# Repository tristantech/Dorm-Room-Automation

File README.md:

Dorm-Room-Automation
====================

Complete automation system for lights, A/V, doors, etc

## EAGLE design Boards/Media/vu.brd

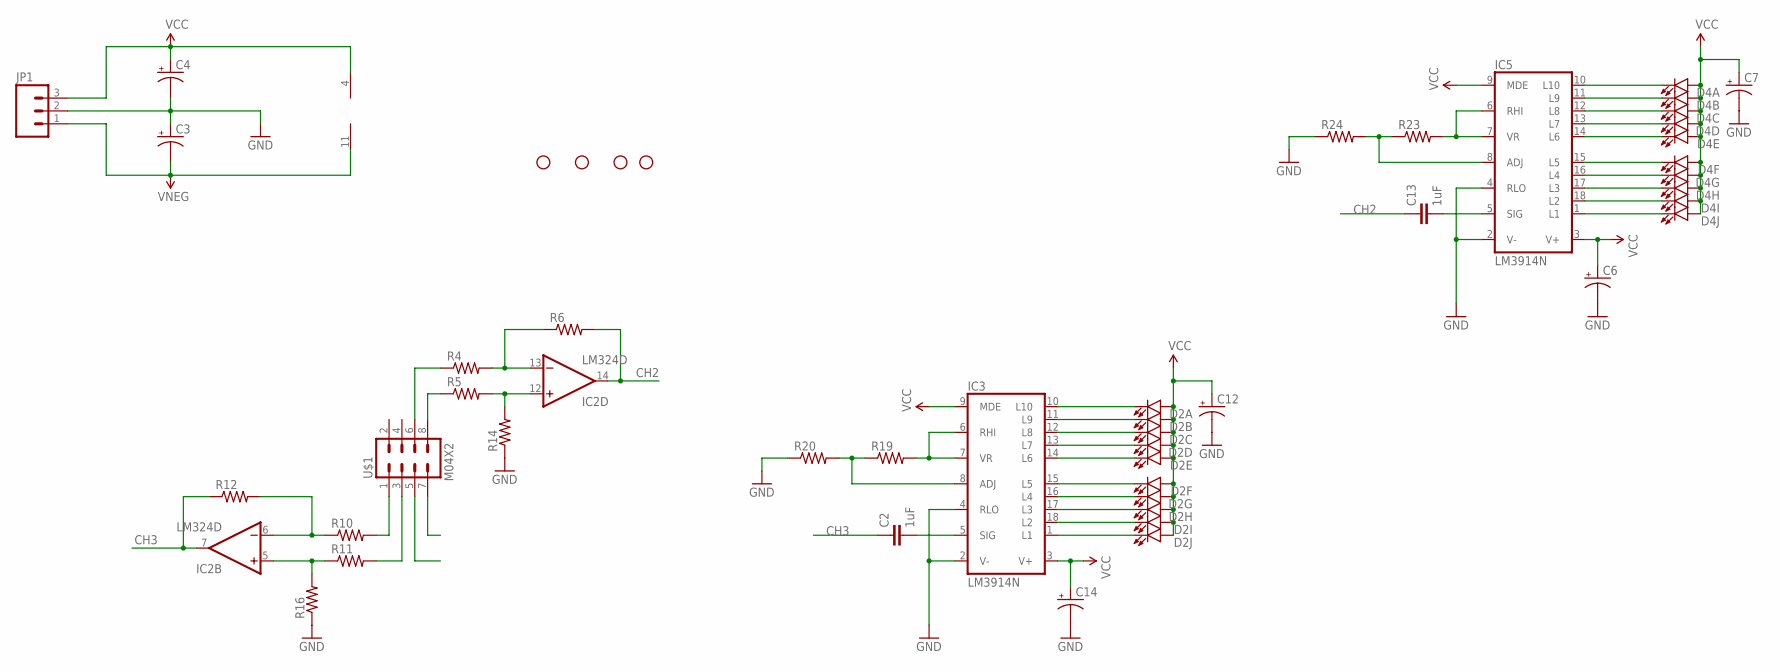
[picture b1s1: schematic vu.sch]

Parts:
C2, C13: 1uF; 1206
C3, C4: CAP_POLPTH1; CPOL-RADIAL-100UF-25V
C6, C7, C12, C14: CAP_POL1206; EIA3216
D2, D4: LED_BARGRAPH_10; LED_BARGAPH_10
IC2: LM324D; SO14
IC3, IC5: LM3914N; DIL18
JP1: M03POLAR; MOLEX-1X3
R4, R5, R6, R10, R11, R12, R14, R16: RESISTOR0603; 0603-RES
R19, R20, R23, R24: RESISTOR1206; 1206
STANDOFF1, STANDOFF2, STANDOFF3, STANDOFF4: STAND-OFF
U$1: M04X2; 2X4

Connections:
CH2: C13.1, IC2.14 (OUT), R6.2
CH3: C2.1, IC2.7 (OUT), R12.1
GND: C3.1 (+), C4.2 (-), C6.C (-), C7.C (-), C12.C (-), C14.C (-), IC3.2 (V-), IC3.4 (RLO), IC5.2 (V-), IC5.4 (RLO), JP1.2, R14.1, R16.1, R20.1, R24.1
unnamed: R11.2, U$1.3
unnamed: R10.2, U$1.1
unnamed: IC2.12 (+IN), R5.2, R14.2
unnamed: R4.1, U$1.6
unnamed: IC2.6 (-IN), R10.1, R12.2
unnamed: IC2.5 (+IN), R11.1, R16.2
unnamed: R5.1, U$1.8
unnamed: IC2.13 (-IN), R4.2, R6.1
unnamed: D2.19 (C), IC3.11 (L9)
unnamed: D2.18 (C), IC3.12 (L8)
unnamed: D2.17 (C), IC3.13 (L7)
unnamed: D2.16 (C), IC3.14 (L6)
unnamed: D2.15 (C), IC3.15 (L5)
unnamed: D2.14 (C), IC3.16 (L4)
unnamed: D2.13 (C), IC3.17 (L3)
unnamed: D2.12 (C), IC3.18 (L2)
unnamed: D2.11 (C), IC3.1 (L1)
unnamed: D2.20 (C), IC3.10 (L10)
unnamed: C2.2, IC3.5 (SIG)
unnamed: IC3.6 (RHI), IC3.7 (VR), R19.2
unnamed: IC3.8 (ADJ), R19.1, R20.2
unnamed: D4.19 (C), IC5.11 (L9)
unnamed: D4.18 (C), IC5.12 (L8)
unnamed: D4.17 (C), IC5.13 (L7)
unnamed: D4.16 (C), IC5.14 (L6)
unnamed: D4.15 (C), IC5.15 (L5)
unnamed: D4.14 (C), IC5.16 (L4)
unnamed: D4.13 (C), IC5.17 (L3)
unnamed: D4.12 (C), IC5.18 (L2)
unnamed: D4.11 (C), IC5.1 (L1)
unnamed: D4.20 (C), IC5.10 (L10)
unnamed: C13.2, IC5.5 (SIG)
unnamed: IC5.6 (RHI), IC5.7 (VR), R23.2
unnamed: IC5.8 (ADJ), R23.1, R24.2
VCC: C4.1 (+), C6.A (+), C7.A (+), C12.A (+), C14.A (+), D2.1 (A), D2.2 (A), D2.3 (A), D2.4 (A), D2.5 (A), D2.6 (A), D2.7 (A), D2.8 (A), D2.9 (A), D2.10 (A), D4.1 (A), D4.2 (A), D4.3 (A), D4.4 (A), D4.5 (A), D4.6 (A), D4.7 (A), D4.8 (A), D4.9 (A), D4.10 (A), IC2.4 (V+), IC3.3 (V+), IC3.9 (MDE), IC5.3 (V+), IC5.9 (MDE), JP1.3
VNEG: C3.2 (-), IC2.11 (V-), JP1.1

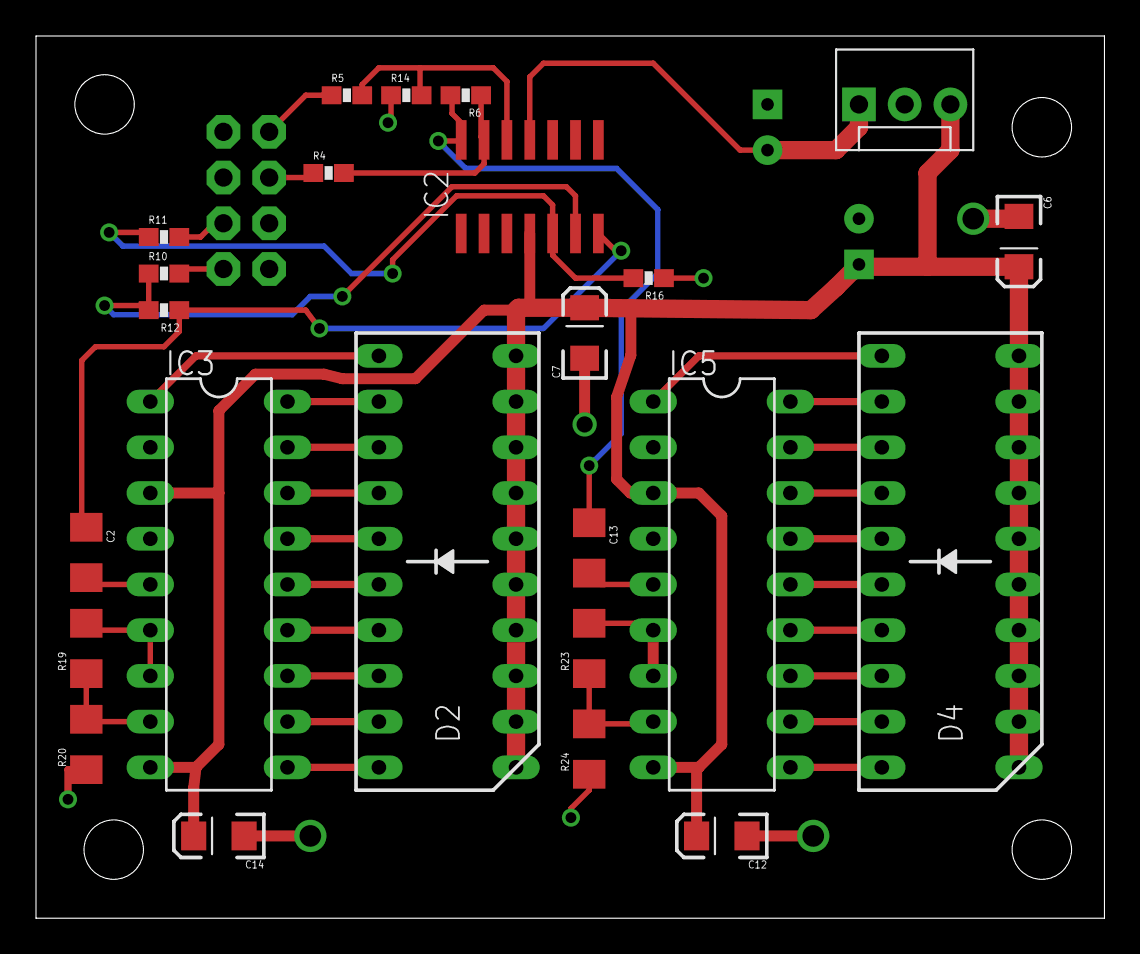
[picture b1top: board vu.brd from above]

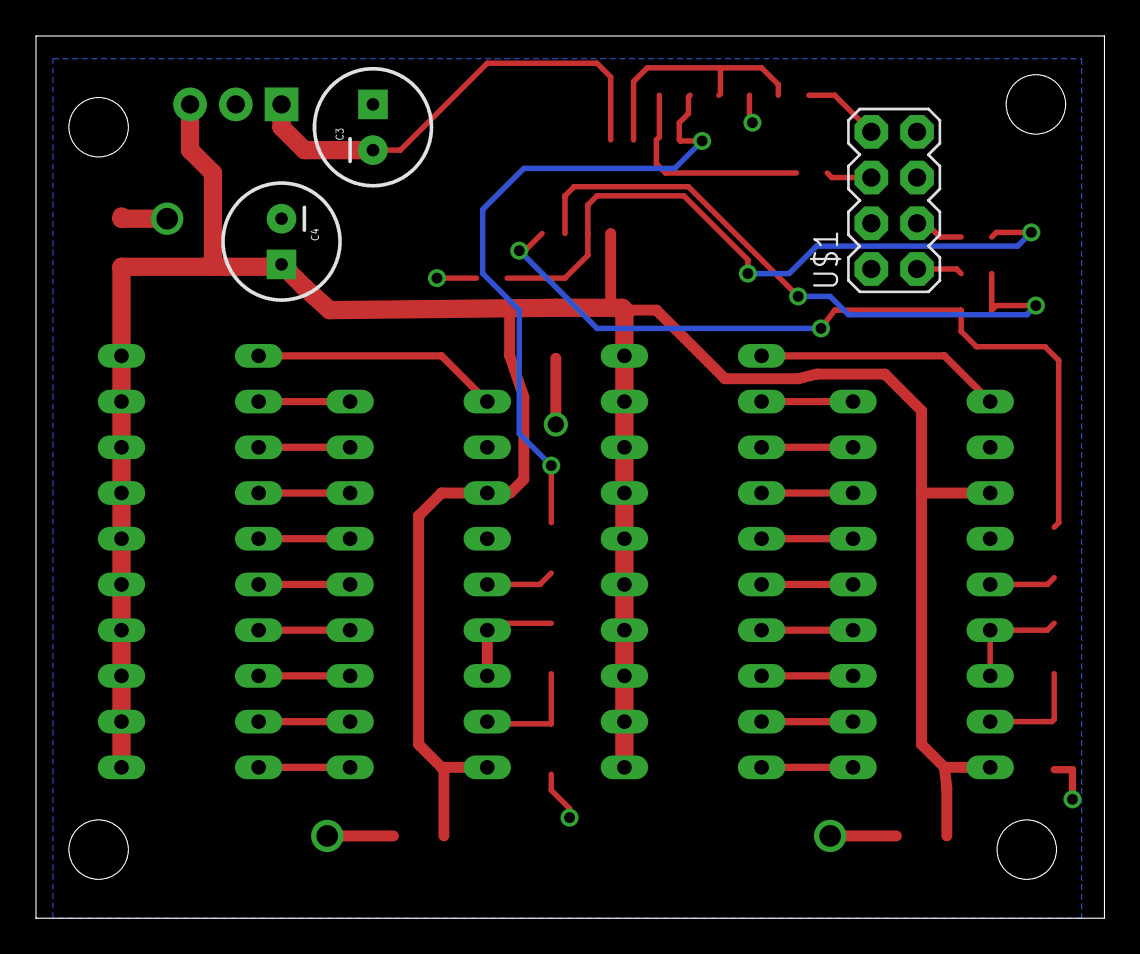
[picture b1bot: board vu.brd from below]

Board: 2 copper layers, 59.4 x 49.0 mm, 31 parts (3 on the bottom side), 39 nets.

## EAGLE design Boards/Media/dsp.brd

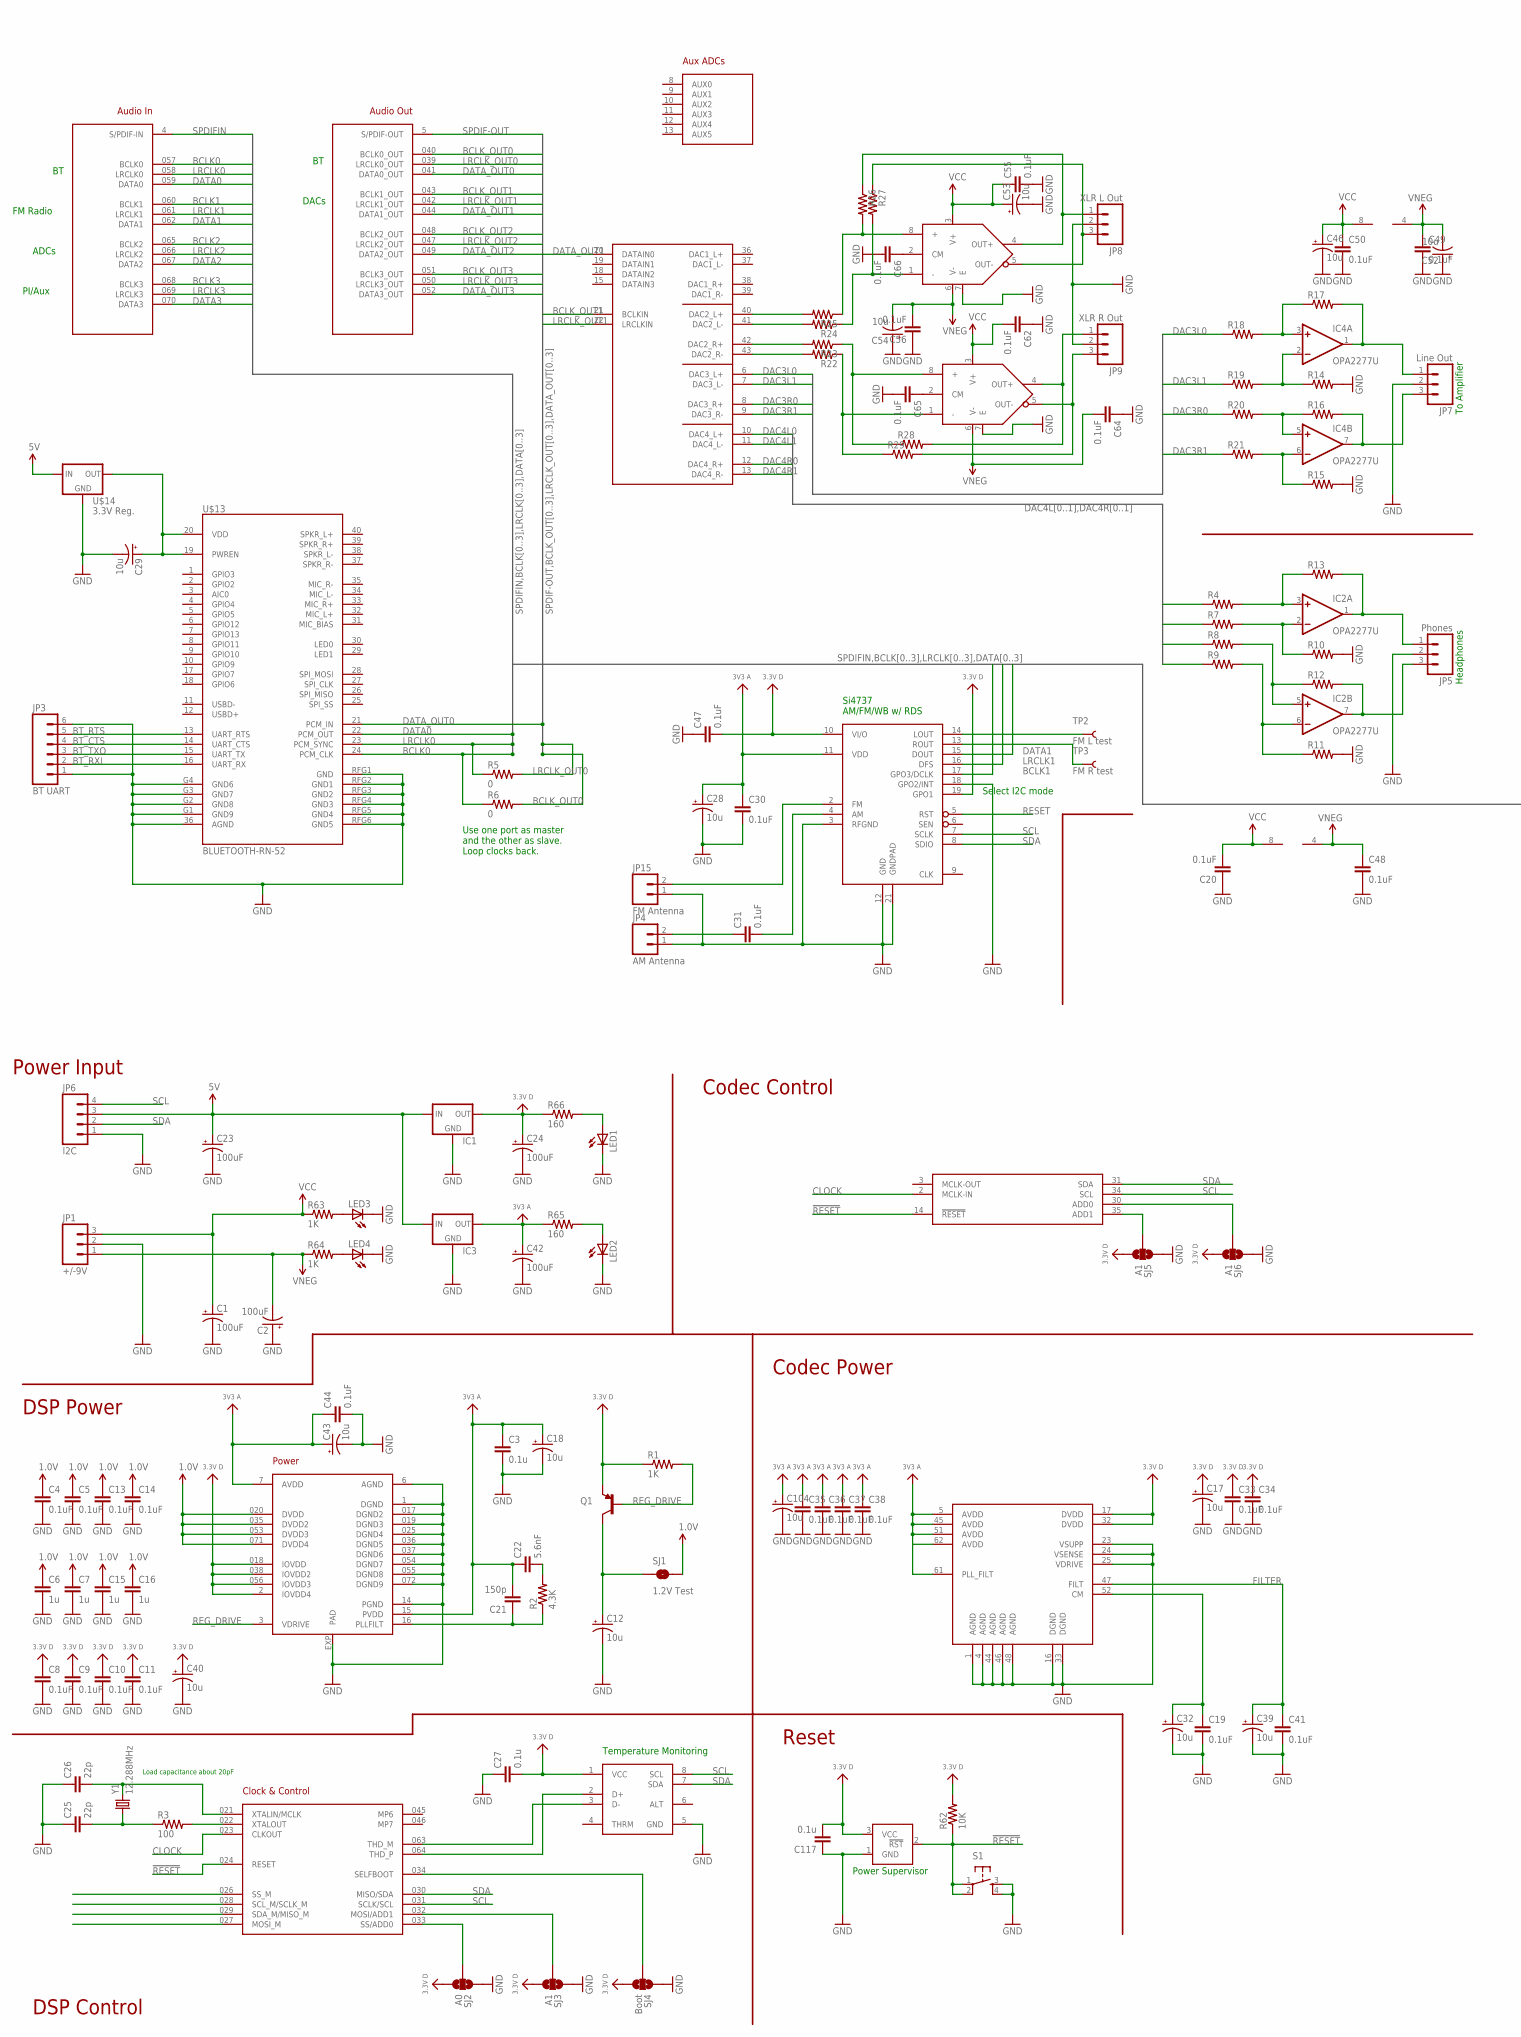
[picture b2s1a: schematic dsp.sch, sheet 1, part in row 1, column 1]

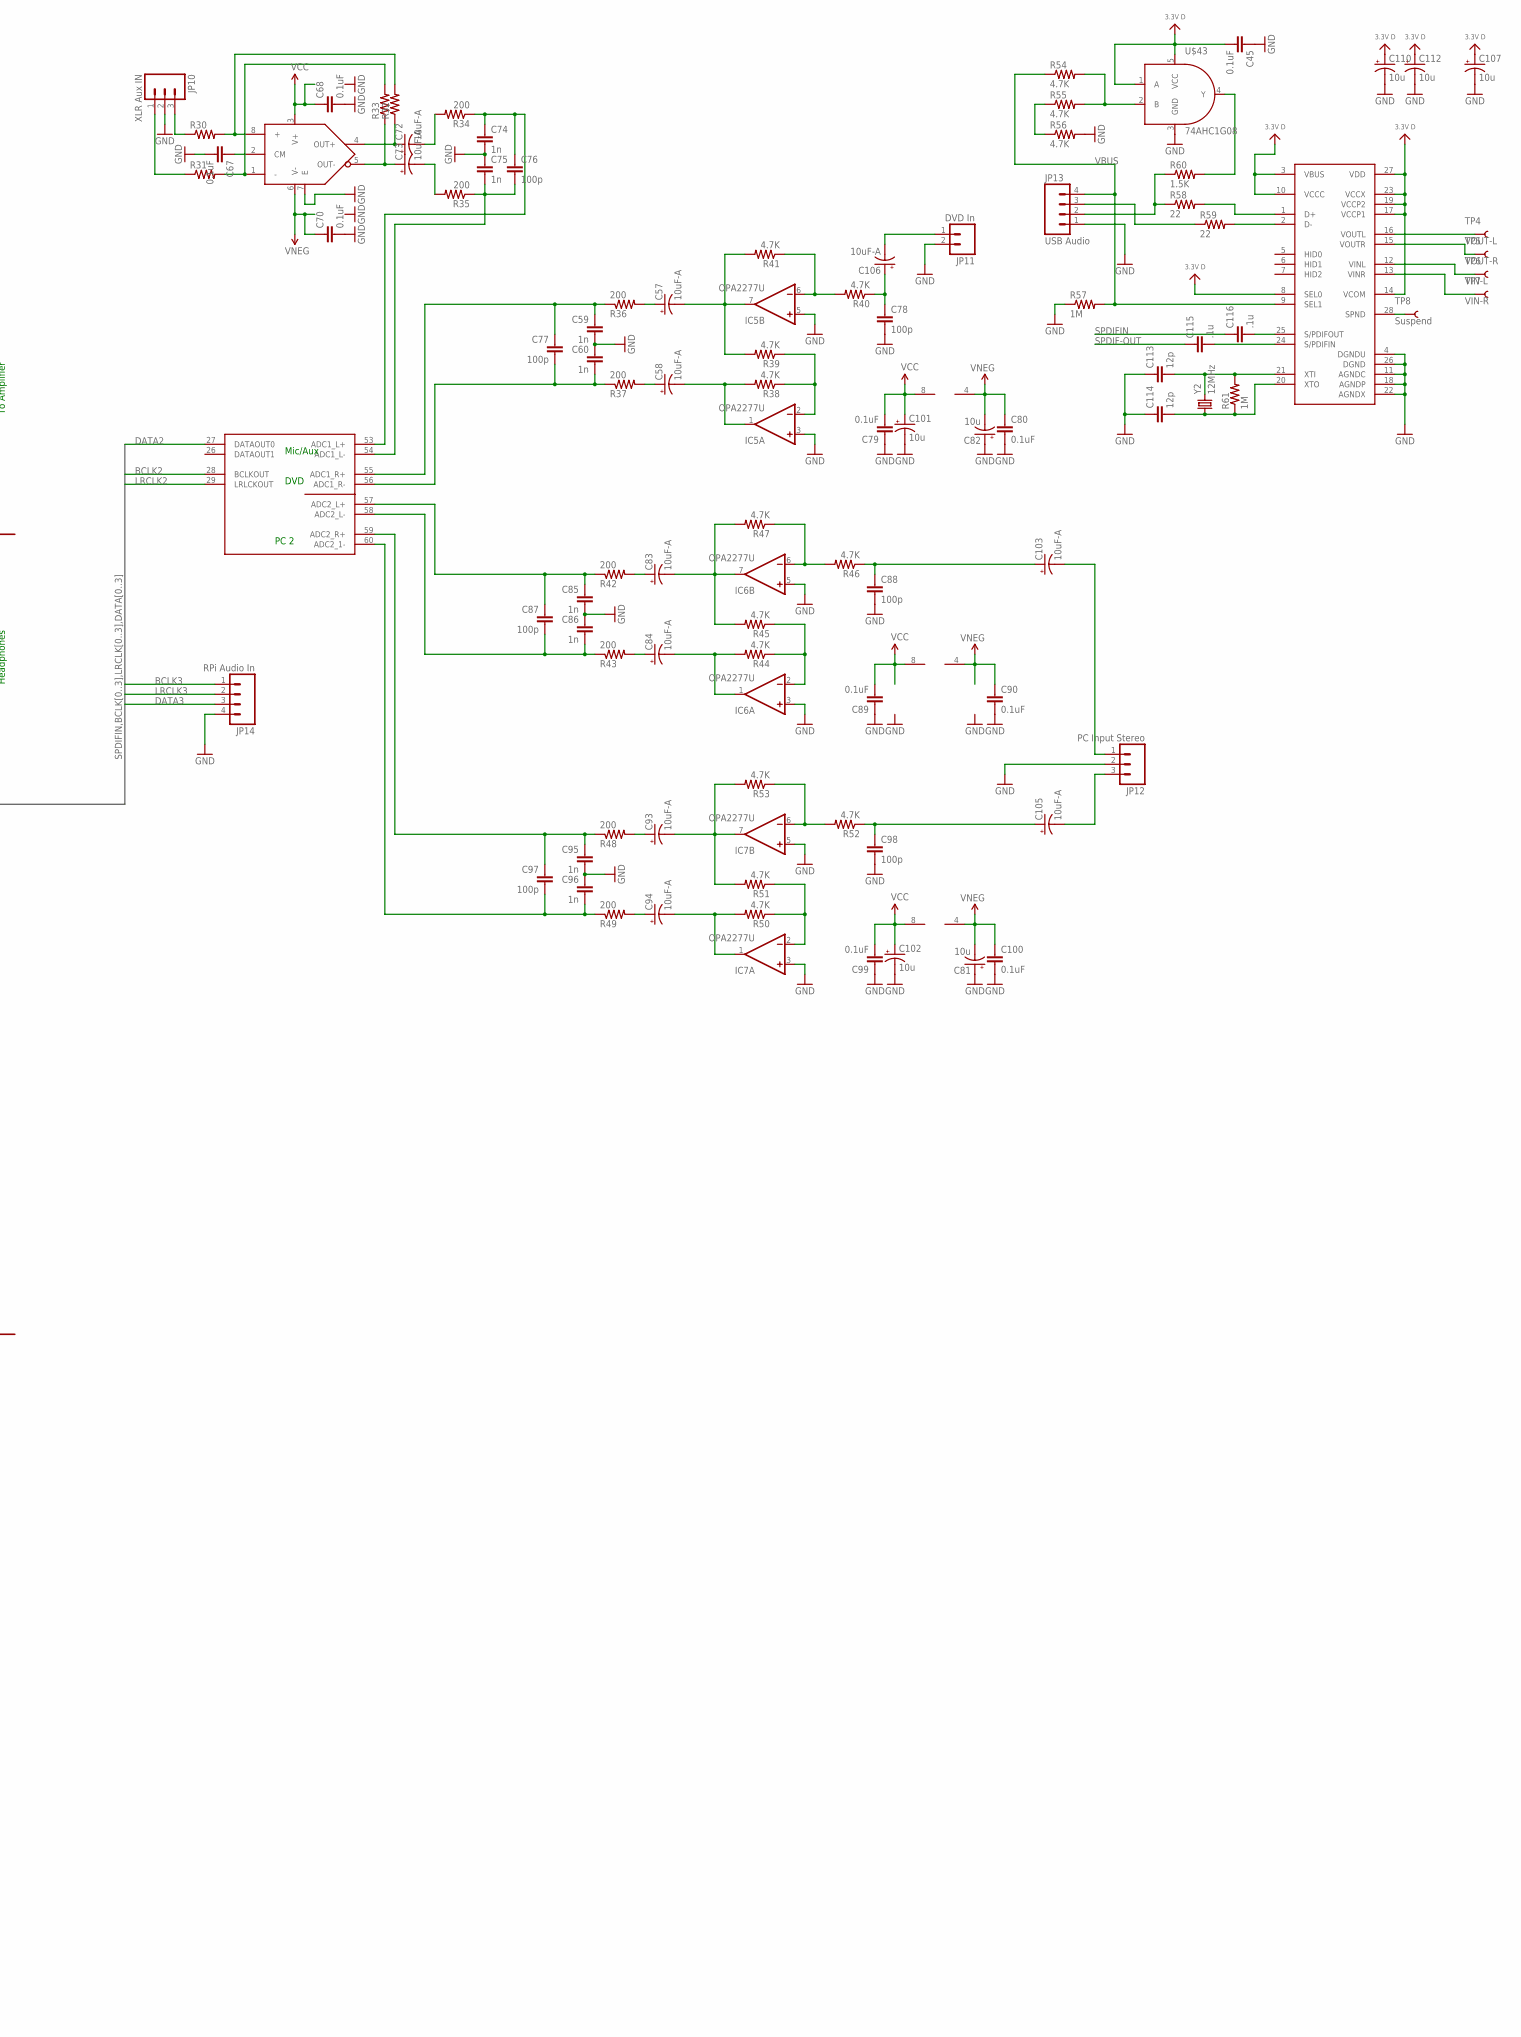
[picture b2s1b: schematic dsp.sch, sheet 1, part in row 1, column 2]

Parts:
C1, C2, C23, C24, C42: 100uF; CPOL-RADIAL-100UF-25V
C3, C27, C117: 0.1u; 0603-CAP
C4, C5, C8, C9, C10, C11, C13, C14, C19, C20, C30, C31, C33, C34, C35, C36, C37, C38, C41, C44, C45, C47, C48, C49, C50, C55, C56, C62, C64, C65, C66, C67, C68, C70, C79, C80, C89, C90, C99, C100: 0.1uF; 0603-CAP
C6, C7, C15, C16: 1u; 0603-CAP
C12, C17, C18, C28, C29, C32, C39, C40, C43, C46, C52, C53, C54, C81, C82, C101, C102, C104, C107, C110, C112: 10u; PANASONIC_B
C21: 150p; 0603-CAP
C22: 5.6nF; 0603-CAP
C25, C26: 22p; 0603-CAP
C57, C58, C72, C73, C83, C84, C93, C94, C103, C105, C106: 10uF-A; PANASONIC_C
C59, C60, C74, C75, C85, C86, C95, C96: 1n; 0603-CAP
C76, C77, C78, C87, C88, C97, C98: 100p; 0603-CAP
C113, C114: 12p; 0603-CAP
C115, C116: .1u; 0603-CAP
IC1, IC3: V_REG_78XXSINK; TO220-IGO
IC2, IC4, IC5, IC6, IC7: OPA2277U; SO08
JP1: +/-9V; MOLEX-1X3
JP3: BT UART; MOLEX-1X6
JP4: AM Antenna; 1X02
JP5: Phones; MOLEX-1X3
JP6: I2C; MOLEX-1X4
JP7: Line Out; MOLEX-1X3
JP8: XLR L Out; MOLEX-1X3
JP9: XLR R Out; MOLEX-1X3
JP10: XLR Aux IN; MOLEX-1X3
JP11: DVD In; MOLEX-1X2
JP12: PC Input Stereo; MOLEX-1X3
JP13: USB Audio; MOLEX-1X4
JP14: RPi Audio In; MOLEX-1X4
JP15: FM Antenna; 1X02
LED1, LED2, LED3, LED4: LED1206; LED-1206
Q1: TRANSISTOR_PNPSMD; SOT23-3
R1, R63, R64: 1K; 1206
R2: 4.3K; 1206
R3: 100; 1206
R4, R7, R8, R9, R10, R11, R12, R13, R14, R15, R16, R17, R18, R19, R20, R21, R22, R23, R24, R25, R26, R27, R28, R29, R30, R31, R32, R33: RESISTOR1206; 1206
R5, R6: 0; 1206
R34, R35, R36, R37, R42, R43, R48, R49: 200; 1206
R38, R39, R40, R41, R44, R45, R46, R47, R50, R51, R52, R53, R54, R55, R56: 4.7K; 1206
R57, R61: 1M; 1206
R58, R59: 22; 1206
R60: 1.5K; 1206
R62: 10K; 1206
R65, R66: 160; 1206
S1: TAC_SWITCHPTH; TACTILE-PTH
SJ1: 1.2V Test; SJ_2S-NO
SJ2: A0; SJ_3
SJ3, SJ5, SJ6: A1; SJ_3
SJ4: Boot; SJ_3
TP2: FM L test; PAD.03X.03
TP3: FM R test; PAD.03X.03
TP4: VOUT-L; PAD.03X.03
TP5: VOUT-R; PAD.03X.03
TP6: VIN-L; PAD.03X.03
TP7: VIN-R; PAD.03X.03
TP8: Suspend; PAD.03X.03
U$1: ADAU1451; LFCSP-72
U$8: ADM1032; MSOP-8
U$13: BLUETOOTH-RN-52; RN-52
U$14: 3.3V Reg.; SOT223
U$15: SI4736/37/38/39; QFN-16
U$17: AD1937; LQFP-64
U$35, U$38, U$39: LME49724; SOIC-8
U$40: PCM2903; SSOP-28
U$43: 74AHC1G08; SOT23-5
U$52: TLV803; SOT23
Y1: 12.288MHz; HC49U-V
Y2: 12MHz; HC49U-V

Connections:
1.0V: C4.1, C5.1, C6.1, C7.1, C13.1, C14.1, C15.1, C16.1, SJ1.2, U$1.020 (DVDD), U$1.035 (DVDD2), U$1.053 (DVDD3), U$1.071 (DVDD4)
3.3V_A: C3.1, C18.+, C21.2, C22.1, C28.+, C30.1, C35.1, C36.1, C37.1, C38.1, C42.1 (+), C43.+, C44.1, C104.+, IC3.OUT, R65.1, U$1.7 (AVDD), U$1.15 (PVDD), U$15.11 (VDD), U$17.5 (AVDD), U$17.45 (AVDD), U$17.51 (AVDD), U$17.61 (PLL_FILT), U$17.62 (AVDD)
3V3_D: C8.1, C9.1, C10.1, C11.1, C17.+, C24.1 (+), C27.2, C33.1, C34.1, C40.+, C45.2, C47.2, C107.+, C110.+, C112.+, C117.2, IC1.OUT, Q1.2 (E), R1.1, R62.2, R66.1, SJ2.3, SJ3.3, SJ4.3, SJ5.3, SJ6.3, U$1.2 (IOVDD4), U$1.018 (IOVDD), U$1.038 (IOVDD2), U$1.056 (IOVDD3), U$8.1 (VCC), U$15.10 (VI/O), U$15.19 (GPO1), U$17.17 (DVDD), U$17.32 (DVDD), U$40.3 (VBUS), U$40.8 (SEL0), U$40.10 (VCCC), U$40.14 (VCOM), U$40.17 (VCCP1), U$40.19 (VCCP2), U$40.23 (VCCX), U$40.27 (VDD), U$43.1 (A), U$43.5 (VCC), U$52.3 (VCC)
5V: C23.1 (+), IC1.IN, IC3.IN, JP6.3, U$14.1 (IN)
!RESET: R62.1, S1.1, S1.2, U$1.024 (RESET), U$17.14 (!RESET), U$52.2 (!RST)
BCLK0: R6.1, U$1.057 (BCLK0), U$13.24 (PCM_CLK)
BCLK1: U$1.060 (BCLK1), U$15.17 (GPO3/DCLK)
BCLK2: U$1.065 (BCLK2), U$17.28 (BCLKOUT)
BCLK3: JP14.1, U$1.068 (BCLK3)
BCLK_OUT0: R6.2, U$1.040 (BCLK0_OUT)
BCLK_OUT1: U$1.043 (BCLK1_OUT), U$17.21 (BCLKIN)
BCLK_OUT2: U$1.048 (BCLK2_OUT)
BCLK_OUT3: U$1.051 (BCLK3_OUT)
BT_CTS: JP3.4, U$13.14 (UART_CTS)
BT_RTS: JP3.5, U$13.13 (UART_RTS)
BT_RXI: JP3.2, U$13.16 (UART_RX)
BT_TXO: JP3.3, U$13.15 (UART_TX)
CLOCK: U$1.023 (CLKOUT), U$17.2 (MCLK-IN)
DAC3L0: R18.1, U$17.6 (DAC3_L+)
DAC3L1: R19.1, U$17.7 (DAC3_L-)
DAC3R0: R20.1, U$17.8 (DAC3_R+)
DAC3R1: R21.1, U$17.9 (DAC3_R-)
DAC4L0: R4.1, U$17.10 (DAC4_L+)
DAC4L1: R7.1, U$17.11 (DAC4_L-)
DAC4R0: R8.1, U$17.12 (DAC4_R+)
DAC4R1: R9.1, U$17.13 (DAC4_R-)
DATA0: U$1.059 (DATA0), U$13.22 (PCM_OUT)
DATA1: U$1.062 (DATA1), U$15.15 (DOUT)
DATA2: U$1.067 (DATA2), U$17.27 (DATAOUT0)
DATA3: JP14.3, U$1.070 (DATA3)
DATA_OUT0: U$1.041 (DATA0_OUT), U$13.21 (PCM_IN)
DATA_OUT1: U$1.044 (DATA1_OUT), U$17.20 (DATAIN0)
DATA_OUT2: U$1.049 (DATA2_OUT)
DATA_OUT3: U$1.052 (DATA3_OUT)
FILTER: C39.+, C41.1, U$17.47 (FILT)
FM: JP15.2, U$15.2 (FM)
GND: C1.2 (-), C2.1 (+), C3.2, C4.2, C5.2, C6.2, C7.2, C8.2, C9.2, C10.2, C11.2, C12.-, C13.2, C14.2, C15.2, C16.2, C17.-, C18.-, C19.2, C20.1, C23.2 (-), C24.2 (-), C25.1, C26.1, C27.1, C28.-, C29.-, C30.2, C32.-, C33.2, C34.2, C35.2, C36.2, C37.2, C38.2, C39.-, C40.-, C41.2, C42.2 (-), C43.-, C44.2, C45.1, C46.-, C47.1, C48.2, C49.2, C50.2, C52.+, C53.-, C54.+, C55.2, C56.1, C59.2, C60.1, C62.1, C64.1, C65.2, C66.2, C67.2, C68.2, C70.2, C74.2, C75.1, C78.2, C79.1, C80.2, C81.+, C82.+, C85.2, C86.1, C88.2, C89.1, C90.2, C95.2, C96.1, C98.2, C99.1, C100.2, C101.-, C102.-, C104.-, C107.-, C110.-, C112.-, C113.1, C114.1, C117.1, IC1.GND, IC3.GND, IC5.3 (+IN), IC5.5 (+IN), IC6.3 (+IN), IC6.5 (+IN), IC7.3 (+IN), IC7.5 (+IN), JP1.2, JP3.1, JP3.6, JP4.1, JP5.2, JP6.1, JP7.2, JP8.2, JP9.2, JP10.2, JP11.2, JP12.2, JP13.1, JP14.4, JP15.1, LED1.C, LED2.C, LED3.C, LED4.C, R10.2, R11.2, R14.2, R15.2, R56.2, R57.1, S1.3, S1.4, SJ2.1, SJ3.1, SJ4.1, SJ5.1, SJ6.1, U$1.1 (DGND), U$1.6 (AGND), U$1.14 (PGND), U$1.017 (DGND2), U$1.019 (DGND3), U$1.025 (DGND4), U$1.036 (DGND5), U$1.037 (DGND6), U$1.054 (DGND7), U$1.055 (DGND8), U$1.072 (DGND9), U$1.EXP (PAD), U$8.5 (GND), U$13.36 (AGND), U$13.G1 (GND9), U$13.G2 (GND8), U$13.G3 (GND7), U$13.G4 (GND6), U$13.RFG1 (GND), U$13.RFG2 (GND1), U$13.RFG3 (GND2), U$13.RFG4 (GND3), U$13.RFG5 (GND4), U$13.RFG6 (GND5), U$14.2 (GND), U$15.3 (RFGND), U$15.12 (GND), U$15.18 (GPO2/INT), U$15.21 (GNDPAD), U$17.1 (AGND), U$17.4 (AGND), U$17.16 (DGND), U$17.23 (VSUPP), U$17.24 (VSENSE), U$17.25 (VDRIVE), U$17.33 (DGND), U$17.44 (AGND), U$17.46 (AGND), U$17.48 (AGND), U$35.7 (E), U$38.7 (E), U$39.7 (E), U$40.4 (DGNDU), U$40.11 (AGNDC), U$40.18 (AGNDP), U$40.22 (AGNDX), U$40.26 (DGND), U$43.3 (GND), U$52.1 (GND)
LRCLK0: R5.1, U$1.058 (LRCLK0), U$13.23 (PCM_SYNC)
LRCLK1: U$1.061 (LRCLK1), U$15.16 (DFS)
LRCLK2: U$1.066 (LRCLK2), U$17.29 (LRLCKOUT)
LRCLK3: JP14.2, U$1.069 (LRCLK3)
LRCLK_OUT0: R5.2, U$1.039 (LRCLK0_OUT)
LRCLK_OUT1: U$1.042 (LRCLK1_OUT), U$17.22 (LRCLKIN)
LRCLK_OUT2: U$1.047 (LRCLK2_OUT)
LRCLK_OUT3: U$1.050 (LRCLK3_OUT)
unnamed: C21.1, R2.1, U$1.16 (PLLFILT)
unnamed: C22.2, R2.2
unnamed: R3.2, U$1.022 (XTALOUT)
unnamed: C12.+, Q1.3 (C), SJ1.1
unnamed: C26.2, U$1.021 (XTALIN/MCLK), Y1.2
unnamed: C25.2, R3.1, Y1.1
unnamed: C19.1, C32.+, U$17.52 (CM)
unnamed: U$1.063 (THD_M), U$8.3 (D-)
unnamed: U$1.064 (THD_P), U$8.2 (D+)
unnamed: SJ4.2, U$1.034 (SELFBOOT)
unnamed: SJ3.2, U$1.032 (MOSI/ADD1)
unnamed: SJ2.2, U$1.033 (SS/ADD0)
unnamed: C29.+, U$13.19 (PWREN), U$13.20 (VDD), U$14.3 (OUT)
unnamed: IC2.1 (OUT), JP5.1, R13.2
unnamed: IC2.3 (+IN), R4.2, R13.1
unnamed: C31.2, U$15.4 (AM)
unnamed: C31.1, JP4.2
unnamed: TP2.P$1, U$15.14 (LOUT)
unnamed: TP3.P$1, U$15.13 (ROUT)
unnamed: IC2.2 (-IN), R7.2, R10.1
unnamed: SJ5.2, U$17.35 (ADD1)
unnamed: SJ6.2, U$17.30 (ADD0)
unnamed: IC2.5 (+IN), R8.2, R12.1
unnamed: IC2.6 (-IN), R9.2, R11.1
unnamed: IC4.7 (OUT), JP7.3, R16.2
unnamed: IC4.1 (OUT), JP7.1, R17.2
unnamed: IC2.7 (OUT), JP5.3, R12.2
unnamed: IC4.3 (+IN), R17.1, R18.2
unnamed: IC4.2 (-IN), R14.1, R19.2
unnamed: IC4.5 (+IN), R16.1, R20.2
unnamed: IC4.6 (-IN), R15.1, R21.2
unnamed: C73.+, R33.1, U$39.5 (OUT-)
unnamed: JP9.1, R28.2, U$38.4 (OUT+)
unnamed: JP9.3, R29.2, U$38.5 (OUT-)
unnamed: JP8.1, R26.1, U$35.4 (OUT+)
unnamed: JP8.3, R27.1, U$35.5 (OUT-)
unnamed: R24.2, U$17.41 (DAC2_L-)
unnamed: C66.1, U$35.2 (CM)
unnamed: C65.1, U$38.2 (CM)
unnamed: R25.2, U$17.40 (DAC2_L+)
unnamed: R23.2, U$17.42 (DAC2_R+)
unnamed: R22.2, U$17.43 (DAC2_R-)
unnamed: C72.+, R32.1, U$39.4 (OUT+)
unnamed: R25.1, R26.2, U$35.8 (+)
unnamed: R24.1, R27.2, U$35.1 (-)
unnamed: R23.1, R28.1, U$38.8 (+)
unnamed: R22.1, R29.1, U$38.1 (-)
unnamed: C67.1, U$39.2 (CM)
unnamed: C72.-, R34.2
unnamed: C73.-, R35.2
unnamed: C57.+, R36.2
unnamed: R30.2, R32.2, U$39.8 (+)
unnamed: JP10.3, R30.1
unnamed: JP10.1, R31.1
unnamed: R31.2, R33.2, U$39.1 (-)
unnamed: C75.2, C76.2, R35.1, U$17.54 (ADC1_L-)
unnamed: C58.+, R37.2
unnamed: C74.1, C76.1, R34.1, U$17.53 (ADC1_L+)
unnamed: C60.2, C77.2, R37.1, U$17.56 (ADC1_R-)
unnamed: C59.1, C77.1, R36.1, U$17.55 (ADC1_R+)
unnamed: C58.-, IC5.1 (OUT), R38.2
unnamed: C57.-, IC5.7 (OUT), R39.2, R41.2
unnamed: IC5.2 (-IN), R38.1, R39.1
unnamed: IC5.6 (-IN), R40.2, R41.1
unnamed: C106.-, JP11.1
unnamed: C83.+, R42.2
unnamed: C86.2, C87.2, R43.1, U$17.58 (ADC2_L-)
unnamed: C85.1, C87.1, R42.1, U$17.57 (ADC2_L+)
unnamed: C84.+, R43.2
unnamed: C83.-, IC6.7 (OUT), R45.2, R47.2
unnamed: C84.-, IC6.1 (OUT), R44.2
unnamed: IC6.2 (-IN), R44.1, R45.1
unnamed: IC6.6 (-IN), R46.2, R47.1
unnamed: C88.1, C103.+, R46.1
unnamed: C93.+, R48.2
unnamed: C96.2, C97.2, R49.1, U$17.60 (ADC2_1-)
unnamed: C95.1, C97.1, R48.1, U$17.59 (ADC2_R+)
unnamed: C94.+, R49.2
unnamed: C93.-, IC7.7 (OUT), R51.2, R53.2
unnamed: C94.-, IC7.1 (OUT), R50.2
unnamed: IC7.2 (-IN), R50.1, R51.1
unnamed: IC7.6 (-IN), R52.2, R53.1
unnamed: C98.1, C105.+, R52.1
unnamed: C103.-, JP12.1
unnamed: C105.-, JP12.3
unnamed: C78.1, C106.+, R40.1
unnamed: TP4.P$1, U$40.16 (VOUTL)
unnamed: TP5.P$1, U$40.15 (VOUTR)
unnamed: TP6.P$1, U$40.12 (VINL)
unnamed: TP7.P$1, U$40.13 (VINR)
unnamed: JP13.2, R58.1, R60.1
unnamed: R58.2, U$40.1 (D+)
unnamed: R54.2, R55.2, U$43.2 (B)
unnamed: R59.2, U$40.2 (D-)
unnamed: R55.1, R56.1
unnamed: JP13.3, R59.1
unnamed: R60.2, U$43.4 (Y)
unnamed: C113.2, R61.2, U$40.21 (XTI), Y2.2
unnamed: TP8.P$1, U$40.28 (SPND)
unnamed: C114.2, R61.1, U$40.20 (XTO), Y2.1
unnamed: C115.2, U$40.24 (S/PDIFIN)
unnamed: C116.2, U$40.25 (S/PDIFOUT)
unnamed: LED3.A, R63.2
unnamed: LED4.A, R64.2
unnamed: LED1.A, R66.2
unnamed: LED2.A, R65.2
REG_DRIVE: Q1.1 (B), R1.2, U$1.3 (VDRIVE)
RESET: U$15.5 (RST)
SCL: JP6.4, U$1.031 (SCLK/SCL), U$8.8 (SCL), U$15.7 (SCLK), U$17.34 (SCL)
SDA: JP6.2, U$1.030 (MISO/SDA), U$8.7 (SDA), U$15.8 (SDIO), U$17.31 (SDA)
SPDIF-OUT: C115.1, U$1.5 (S/PDIF-OUT)
SPDIFIN: C116.1, U$1.4 (S/PDIF-IN)
VBUS: JP13.4, R54.1, R57.2, U$40.9 (SEL1)
VCC: C1.1 (+), C20.2, C46.+, C50.1, C53.+, C55.1, C62.2, C68.1, C79.2, C89.2, C99.2, C101.+, C102.+, IC2.8 (V+), IC4.8 (V+), IC5.8 (V+), IC6.8 (V+), IC7.8 (V+), JP1.3, R63.1, U$35.3 (V+), U$38.3 (V+), U$39.3 (V+)
VNEG: C2.2 (-), C48.1, C49.1, C52.-, C54.-, C56.2, C64.2, C70.1, C80.1, C81.-, C82.-, C90.1, C100.1, IC2.4 (V-), IC4.4 (V-), IC5.4 (V-), IC6.4 (V-), IC7.4 (V-), JP1.1, R64.1, U$35.6 (V-), U$38.6 (V-), U$39.6 (V-)

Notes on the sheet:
Load capacitance about 20pF
Temperature Monitoring
Use one port as master and the other as slave. Loop clocks back.
Si4737 AM/FM/WB w/ RDS
FM Radio
Select I2C mode
Power Input
DSP Power
DSP Control
Codec Power
Codec Control
Headphones
To Amplifier
Mic/Aux
PC 2
DVD
ADCs
DACs
Reset
PI/Aux
Power Supervisor

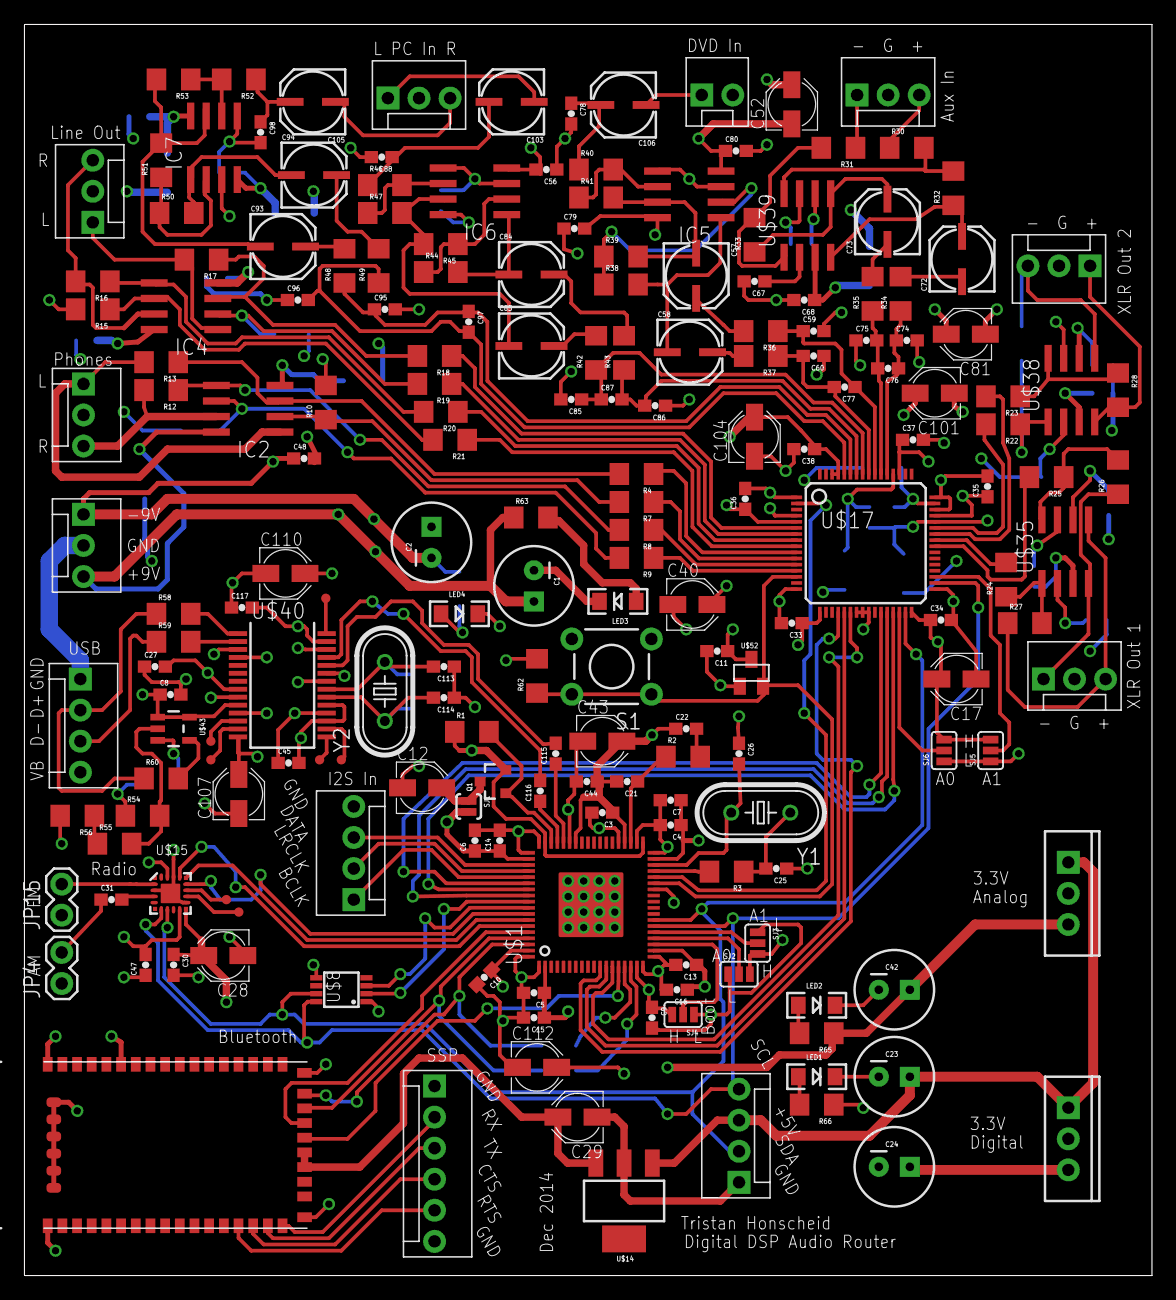
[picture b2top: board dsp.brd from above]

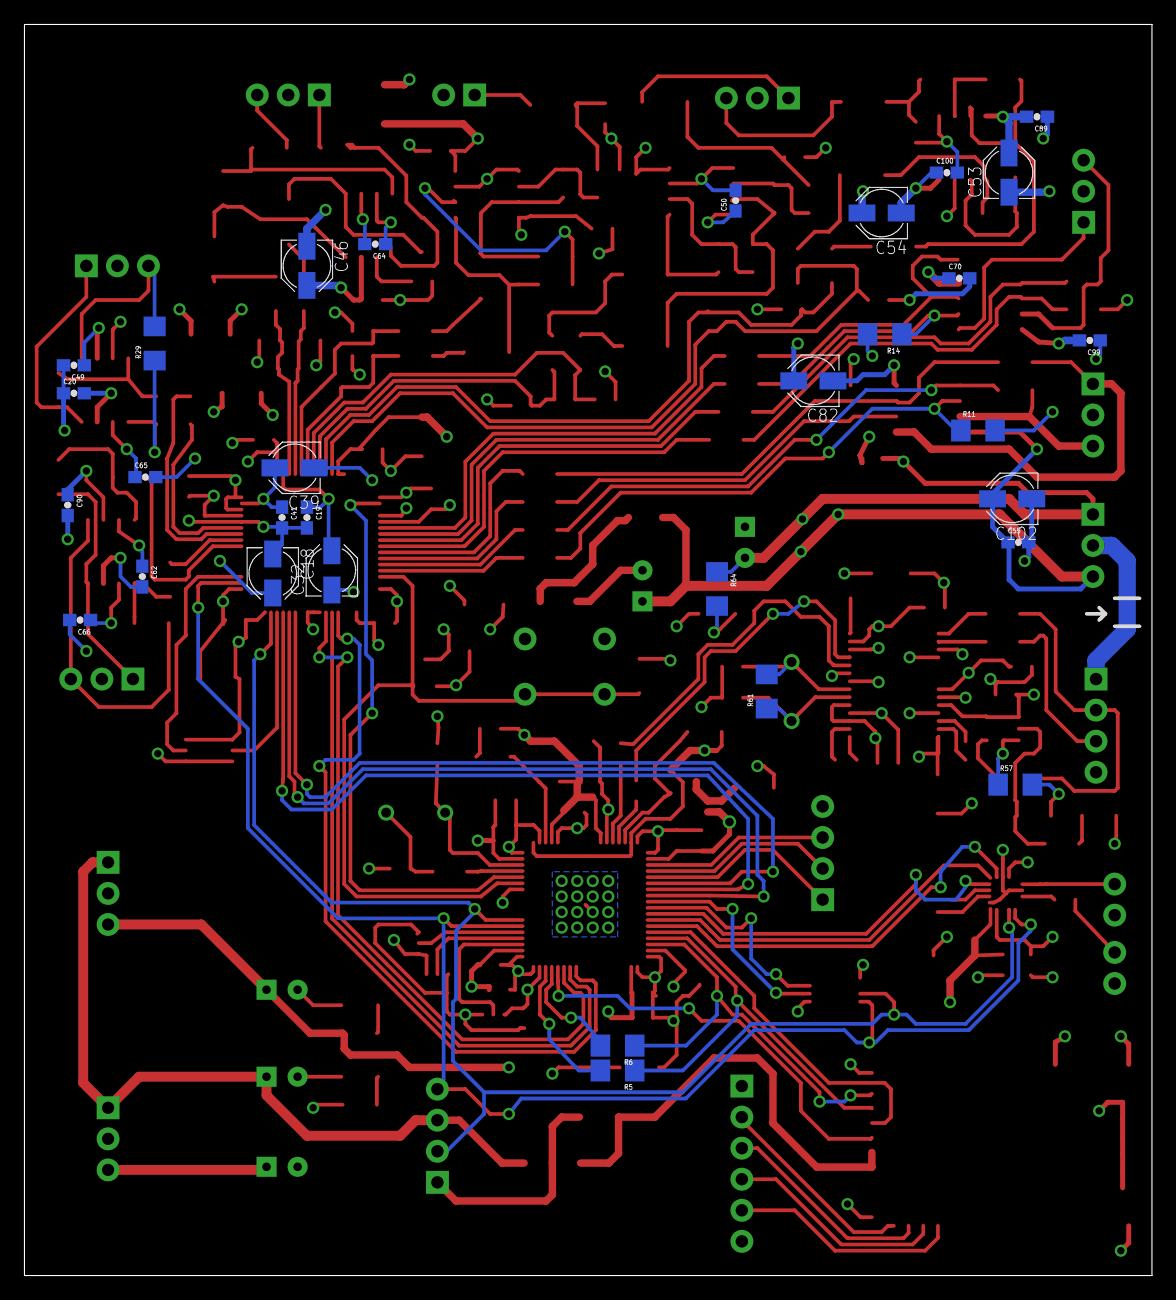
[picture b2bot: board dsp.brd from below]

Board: 4 copper layers, 92.2 x 102.3 mm, 227 parts (31 on the bottom side), 153 nets.

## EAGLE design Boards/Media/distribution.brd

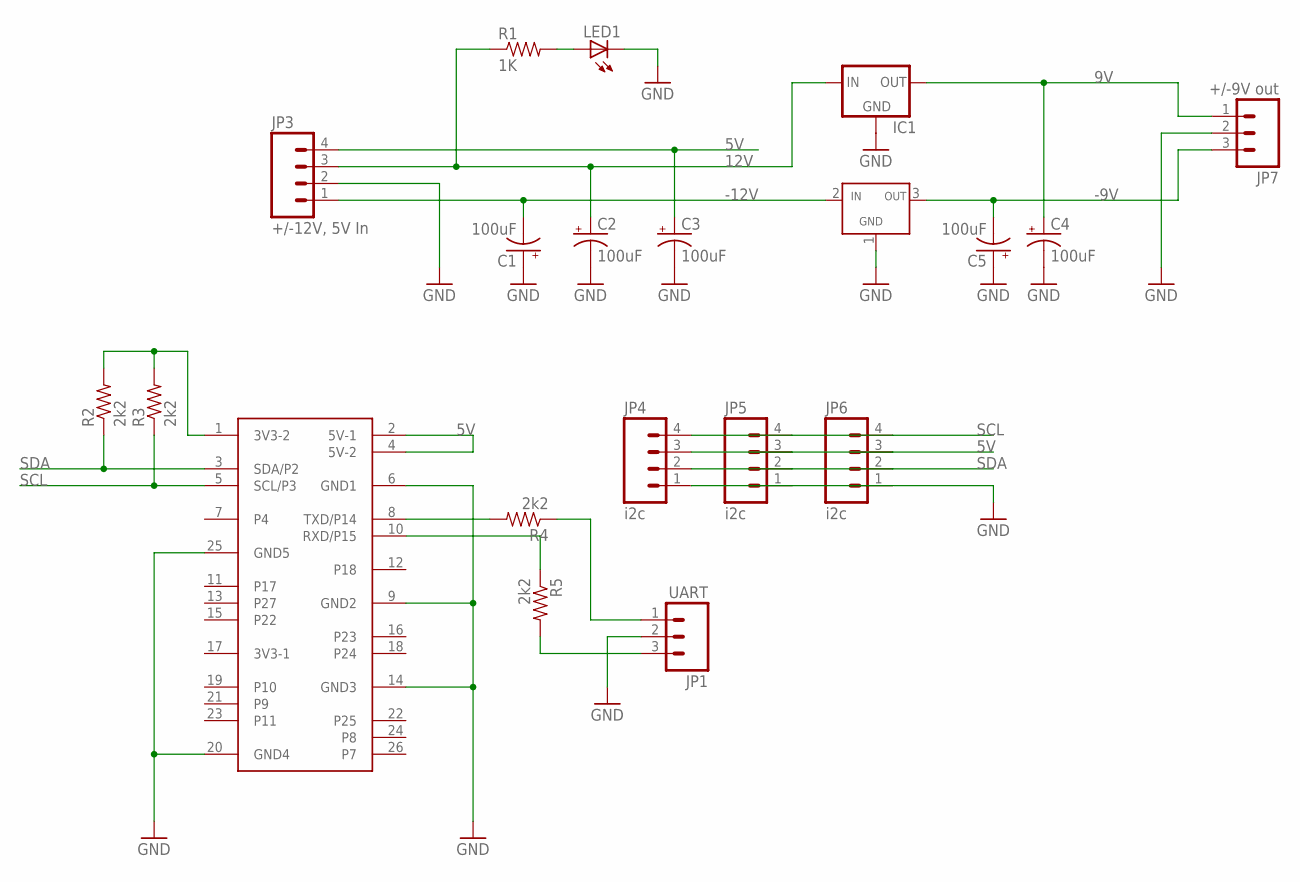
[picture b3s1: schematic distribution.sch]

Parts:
C1, C2, C3, C4, C5: 100uF; CPOL-RADIAL-100UF-25V
IC1: 78XXS
JP1: UART; MOLEX-1X3
JP3: +/-12V, 5V In; SCREWTERMINAL-3.5MM-4
JP4, JP5, JP6: i2c; MOLEX-1X4
JP7: +/-9V out; MOLEX-1X3
LED1: LED1206; LED-1206
R1: 1K; 1206
R2, R3, R4, R5: 2k2; 1206
U$1: VREG-GIO; TO-220V
U$2: PI-GPIO; M2X13

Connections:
5V: C3.1 (+), JP3.4, JP4.3, JP5.3, JP6.3, U$2.2 (5V-1), U$2.4 (5V-2)
9V: C4.1 (+), IC1.OUT, JP7.1
12V: C2.1 (+), IC1.IN, JP3.3, R1.1
-9V: C5.2 (-), JP7.3, U$1.3 (OUT)
-12V: C1.2 (-), JP3.1, U$1.2 (IN)
GND: C1.1 (+), C2.2 (-), C3.2 (-), C4.2 (-), C5.1 (+), IC1.GND, JP1.2, JP3.2, JP4.1, JP5.1, JP6.1, JP7.2, LED1.C, U$1.1 (GND), U$2.6 (GND1), U$2.9 (GND2), U$2.14 (GND3), U$2.20 (GND4), U$2.25 (GND5)
unnamed: LED1.A, R1.2
unnamed: R2.2, R3.2, U$2.1 (3V3-2)
unnamed: R4.2, U$2.8 (TXD/P14)
unnamed: R5.1, U$2.10 (RXD/P15)
unnamed: JP1.1, R4.1
unnamed: JP1.3, R5.2
SCL: JP4.4, JP5.4, JP6.4, R3.1, U$2.5 (SCL/P3)
SDA: JP4.2, JP5.2, JP6.2, R2.1, U$2.3 (SDA/P2)

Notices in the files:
parts and their libraries:
1_SparkFun-DigitalIC: Licensing: CC v3.0 Share-Alike You are welcome to use this library for commercial purposes.
